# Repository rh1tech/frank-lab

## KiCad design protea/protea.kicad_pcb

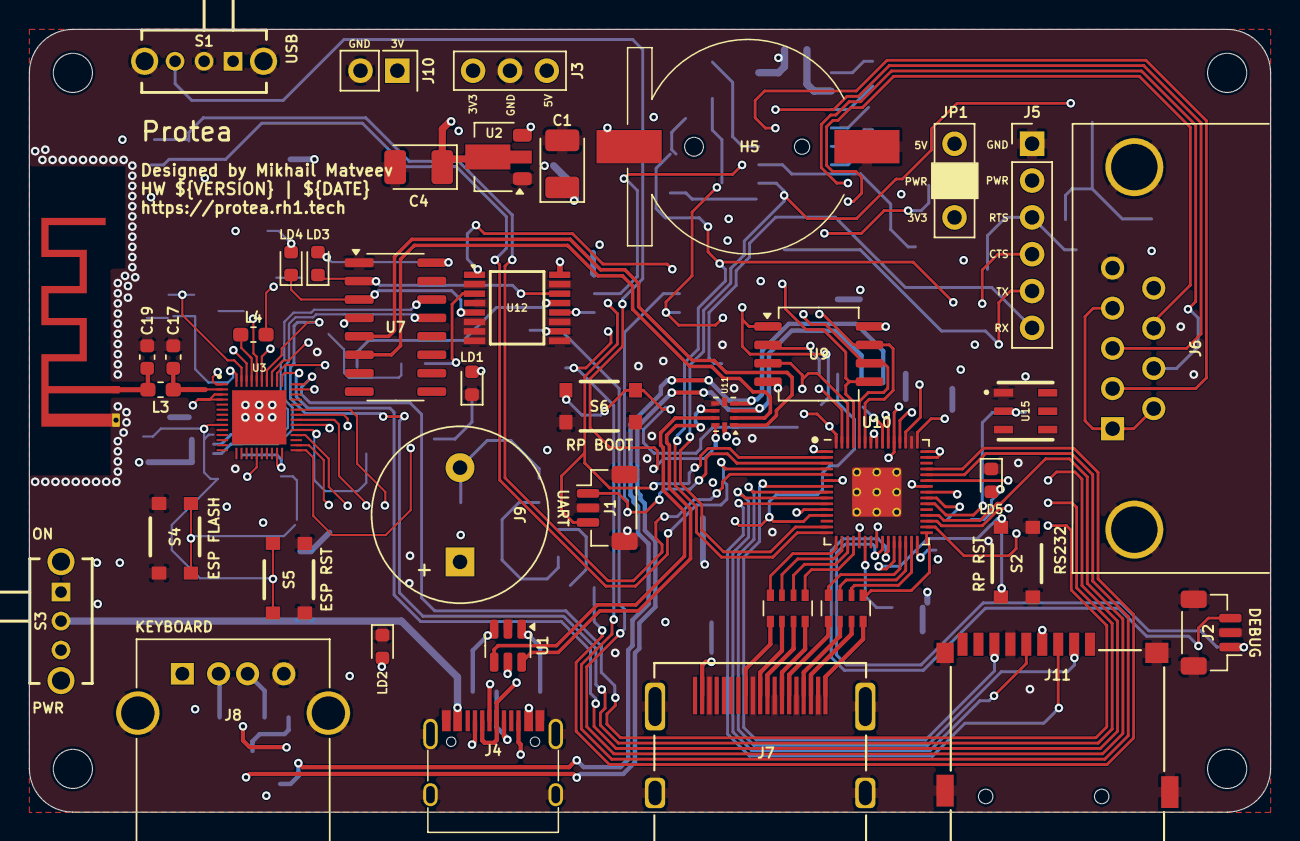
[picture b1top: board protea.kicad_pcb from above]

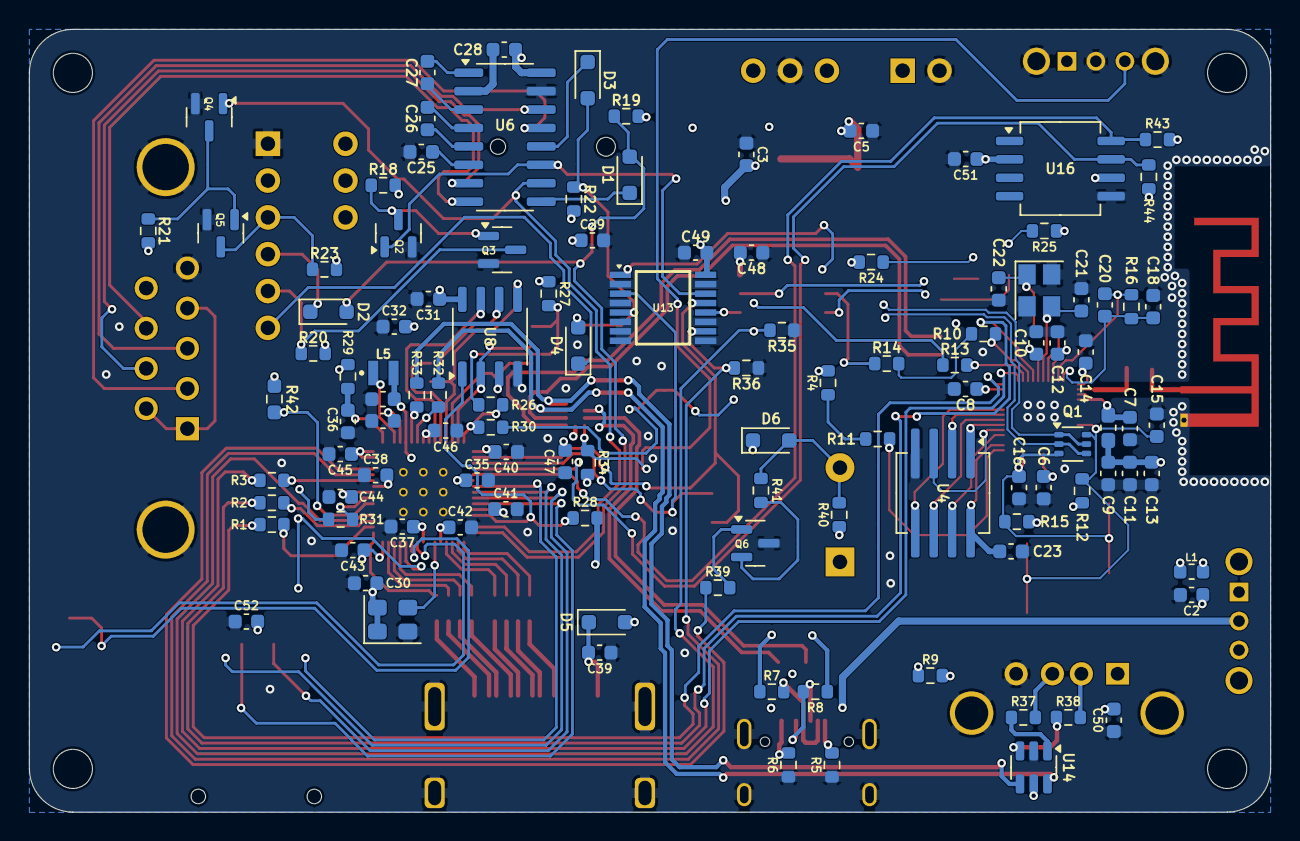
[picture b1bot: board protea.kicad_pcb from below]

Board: 4 copper layers, 85.6 x 54.0 mm, 159 parts (113 on the bottom side), 139 nets.

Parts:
AE1: Antenna_Shield; Antenna_2.4GHz
C1, C4: 22u; CP_Tantalum_3528-12
C2, C3, C5, C29, C30, C31, C32, C35, C38, C39, C40, C41, C42, C43, C44, C45, C46, C47, C51, C52: 100n; C_0603_1608Metric
C6, C13: 1u; C_0603_1608Metric_HandSolder
C7, C9, C10, C12, C14, C23: 100n; C_0603_1608Metric_HandSolder
C8: 100p; C_0603_1608Metric_HandSolder
C11: 10u; C_0603_1608Metric_HandSolder
C15, C16: 1n; C_0603_1608Metric_HandSolder
C17: 1.5pF; C_0603_1608Metric_HandSolder
C18: 10n; C_0603_1608Metric_HandSolder
C19: 2.4pF; C_0603_1608Metric_HandSolder
C20: 3.3n; C_0603_1608Metric_HandSolder
C21, C22: 12p; C_0603_1608Metric_HandSolder
C25, C26, C27, C28: 1u; C_0603_1608Metric_Small
C33, C34, C36, C37: 4.7u; C_0603_1608Metric
C48, C49: 100n; C_0603_1608Metric_Small
C50: 10u; C_0603_1608Metric
D1, D2, D3, D4: 1N4148; D_SOD-323_Alt
D5: 1N5819WS; D_SOD-323
D6: 1N4148; D_SOD-323
H1, H2, H3, H4: Hole 2.7mm; MountingHole_2.7mm
H5: S8411-45R_1; Battery_CR1220
J1: UART; JST_SH_1x03_P1.00mm_Vertical
J2: DEBUG; JST_SH_1x03_P1.00mm_Vertical
J3: PWR; PinHeader_1x03_P2.54mm
J4: USB4215-03-A; USB_C_Receptacle
J5: TTL; PinHeader_1x06_P2.54mm_Vertical
J6: D-SUB 9 Male; DSUB-9_Male_TopMount
J7: DC3RX19JA2; HDMI_Female
J8: 676430910; USB_A_Single
J9: Buzzer; Buzzer_12x8.5RM6.5
J10: BAT 3V; PinHeader_1x02_P2.54mm_Vertical
J11: 104031-0811; MicroSD_SMD_Long
JP1: TTL PWR; PinHeader_1x03_P2.54mm_Vertical
L1: 330R; L_0603_1608Metric
L2: 2nH; Inductor_0603_1608Metric_HandSolder
L3: 2.7nH/0R; Inductor_0603_1608Metric_HandSolder
L4: 24nH/0R; Inductor_0603_1608Metric_HandSolder
L5: 3.3u; L_pol_2016
LD1, LD5: Blue; LED_0603_1608Metric
LD2: Green; LED_0603_1608Metric
LD3, LD4: Orange; LED_0603_1608Metric
Q1: UMH3N; SOT-363
Q2, Q3, Q4, Q5: 2N7000; SOT-23-2N7000
Q6: BC847; SOT-23
R1, R2, R3, R9, R30, R31, R39: 1K; R_0603_1608Metric
R4: 470R; R_0603_1608Metric
R5, R6: 5.1K; R_0603_1608Metric
R7, R8, R37, R38, R41: 22R; R_0603_1608Metric
R10: 499R; R_0603_1608Metric_HandSolder
R11: 0R; R_0603_1608Metric_HandSolder
R12, R15: 10K; R_0603_1608Metric_HandSolder
R13, R14: 330R; R_0603_1608Metric_HandSolder
R16: 20K; R_0603_1608Metric_HandSolder
R18, R19, R21, R22: 1K; R_0603_1608Metric_Small
R20, R23: 470R; R_0603_1608Metric_Small
R24, R25: 1.5K; R_0603_1608Metric
R26: 0R; R_0603_1608Metric
R27, R28, R34: 10K; R_0603_1608Metric
R29: 33R; R_0603_1608Metric
R32, R33: 27R; R_0603_1608Metric
R35, R36: 10K; R_0603_1608Metric_Small
R40: 300R; R_0603_1608Metric
R42: 4.7K; R_0603_1608Metric_Alt
R43, R44: 4.7K; R_0603_1608Metric
RN1, RN2: 270R; R_Array_4x0603
S1: SK12D07VG3NS; SK12D07VG3NS_USB
S2: RP Reset; KMR_2
S3: SK12D07VG3NS; SK12D07VG3NS_PWR
S4: ESP Flash; KMR_2
S5: ESP Boot; KMR_2
S6: RP BOOT; KMR_2
U1, U14: USBLC6-2SC6; SOT-23-6
U2: AMS1117-3.3; SOT-89-3
U3: ESP32-D0WD-V3; QFN35P500X500X90-49N-D
U4: W25Q32JVSIQ; SOIC-8_Longer
U6: MAX232CSE+; SOP-16
U7: CH340C; SOP-16
U8: ESP-PSRAM32; SO-8
U9: W25Q128JVS; SOIC-8
U10: RP2350; QFN-60_RP2350A
U11: TS3USB221RSER; UQFN-10
U12, U13: 74HC4052; SOP65P640X110-16N
U15: DS2401P+; TSOC-6
U16: DS3231MZ; SOIC-8
Y1: 40MHz; Crystal_SMD_3225-4Pin_3.2x2.5mm
Y2: ASE-12MHz; Oscillator_SMD_4Pin_3.2x2.5mm

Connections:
+1V1: C34.1, C35.1, C37.1, C38.1, L5.1, U10.6 (DVDD), U10.23 (DVDD), U10.39 (DVDD), U10.50 (VREG_FB)
+3.3VP: C7.1, L2.2, U3.3 (VDD3P3_1), U3.4 (VDD3P3_2)
+3V3: C4.1, C5.2, C6.1, C8.1, C9.1, C10.1, C11.1, C12.1, C13.1, C14.1, C29.1, C30.1, C31.1, C32.1, C33.1, C40.1, C41.1, C42.1, C43.1, C44.1, C45.1, C46.1, C47.2, C48.2, C49.2, C51.1, C52.2, J3.1, J11.4 (VDD), JP1.3, L2.1, R9.2, R12.2, R15.2, R18.2, R19.2, R21.2, R22.2, R24.2, R25.1, R27.1, R28.2, R29.1, R34.1, R42.1, R43.2, R44.2, U2.2 (VO), U3.1 (VDDA_1), U3.19 (VDD3P3_RTC), U3.37 (VDD3P3_CPU), U3.43 (VDDA_2), U3.46 (VDDA_3), U7.4 (3V), U7.16 (VCC), U8.8 (VCC), U9.8 (VCC), U10.1 (IOVDD), U10.11 (IOVDD), U10.20 (IOVDD), U10.30 (IOVDD), U10.38 (IOVDD), U10.44 (ADC_AVDD), U10.45 (IOVDD), U10.49 (VREG_VIN), U10.53 (USB_OTP_VDD), U10.54 (QSPI_IOVDD), U11.10 (VCC), U12.16 (VCC), U13.16 (VCC), U16.2 (VCC), Y2.1 (EN), Y2.4 (Vdd)
/CH340C/D+: U7.5 (D+), U11.1 (1D+)
/CH340C/D-: U7.6 (D-), U11.2 (1D-)
/CH340C/DTR: Q1.2 (B1), Q1.4 (E2), U7.13 (DTR)
/CH340C/RTS: Q1.1 (E1), Q1.5 (B2), U7.14 (RTS)
/CH340C/RXD: LD4.1 (K), U7.3 (RxD), U12.5 (2Y1)
/CH340C/TXD: LD3.1 (K), U7.2 (TxD), U12.14 (1Y1)
/DS2401P+/DATA: R42.2, U10.36 (GPIO24), U15.2 (DATA)
/ESP32/ANT: AE1.1 (A), C19.1, L3.1
/ESP32/CAP1: C18.1, C20.1, R16.2, U3.48 (CAP1)
/ESP32/CAP2: C20.2, R16.1, U3.47 (CAP2)
/ESP32/GPIO16: R4.1, R11.2
/ESP32/GPIO19: R1.2, U3.38 (GPIO19)
/ESP32/GPIO21: R2.2, U3.42 (GPIO21)
/ESP32/GPIO22: R3.2, U3.39 (GPIO22)
/ESP32/LNA_IN: C17.1, L3.2, U3.2 (LNA_IN)
/ESP32/RXD: R13.1, U12.13 (1Z)
/ESP32/SCK/CLK: U3.31 (SD_CLK), U4.6 (CLK)
/ESP32/SCS/CMD: U3.30 (SD_CMD), U4.1 (~CS)
/ESP32/SDI/SD1: U3.33 (SD_DATA_1), U4.5 (DI(IO0))
/ESP32/SDO/SD0: U3.32 (SD_DATA_0), U4.2 (DO(IO1))
/ESP32/SHD/SD2: U3.28 (SD_DATA_2), U4.7 (IO3)
/ESP32/SWP/SD3: U3.29 (SD_DATA_3), U4.3 (IO2)
/ESP32/TXD: R14.1, U12.3 (2Z)
/ESP32/U0RXD: R13.2, U3.40 (U0RXD)
/ESP32/U0TXD: R10.2, R14.2
/ESP32/VDD_SDIO: C23.1, U3.26 (VDD_SDIO), U4.8 (VCC)
/ESP32/XTAL_N: C21.1, U3.44 (XTAL_N), Y1.3
/ESP32/XTAL_P: L4.1, U3.45 (XTAL_P)
/ESP Buttons/ESP_FLASH: C16.1, Q1.3 (C2), R15.1, S4.2, S4.4, U3.23 (GPIO0)
/ESP Buttons/ESP_RESET: C15.1, Q1.6 (C1), R12.1, S5.2, S5.4, U3.9 (CHIP_PU)
/GPIO0: J1.1, U10.2 (GPIO0), U13.13 (1Z)
/GPIO1: J1.3, U10.3 (GPIO1), U13.3 (2Z)
/GPIO2: R44.1, U10.4 (GPIO2), U16.7 (SDA)
/GPIO3: R43.1, U10.5 (GPIO3), U16.8 (SCL)
/GPIO4: J11.7 (DAT0), U10.7 (GPIO4)
/GPIO5: J11.2 (DAT3/CD), U10.8 (GPIO5)
/GPIO6: J11.5 (CLK), U10.9 (GPIO6)
/GPIO7: J11.3 (CMD), U10.10 (GPIO7)
/GPIO10: Q4.2 (G), U6.10 (T2IN), U10.14 (GPIO10)
/GPIO11: D1.2 (A), D2.2 (A), R19.1, U10.15 (GPIO11)
/GPIO12: RN1.4 (R4.1), U10.16 (GPIO12)
/GPIO13: RN1.3 (R3.1), U10.17 (GPIO13)
/GPIO14: RN1.2 (R2.1), U10.18 (GPIO14)
/GPIO15: RN1.1 (R1.1), U10.19 (GPIO15)
/GPIO16: RN2.4 (R4.1), U10.27 (GPIO16)
/GPIO17: RN2.3 (R3.1), U10.28 (GPIO17)
/GPIO18: RN2.2 (R2.1), U10.29 (GPIO18)
/GPIO19: RN2.1 (R1.1), U10.31 (GPIO19)
/GPIO20: R1.1, U10.32 (GPIO20)
/GPIO21: R2.1, U10.33 (GPIO21)
/GPIO22: R35.2, U10.34 (GPIO22), U12.10 (S0)
/GPIO26: R3.1, U10.40 (GPIO26_ADC0)
/GPIO27: R36.2, U10.41 (GPIO27_ADC1), U13.10 (S0)
/GPIO28: R39.1, U10.42 (GPIO28_ADC2)
/Multiplexers/MP_RX: U12.12 (1Y0), U13.12 (1Y0)
/Multiplexers/MP_TX: U12.1 (2Y0), U13.1 (2Y0)
/Multiplexers/RS232_RX: Q2.2 (G), U6.11 (T1IN), U13.14 (1Y1)
/Multiplexers/RS232_TX: D3.2 (A), D4.2 (A), R22.1, U13.5 (2Y1)
/Power/D+: U1.4 (I/O2), U11.8 (D+)
/Power/D-: U1.6 (I/O1), U11.7 (D-)
/Power/VBUS_IN: J4.2 (VBUS), J4.11 (VBUS), S3.2
/RP2350A/D+: R32.1, U11.3 (2D+), U14.6 (I/O1)
/RP2350A/D-: R33.1, U11.4 (2D-), U14.4 (I/O2)
/RP2350A/FLASH_SS: R26.2, R27.2, U9.1 (~CS)
/RP2350A/GPIO8: R28.1, U8.1 (~CE), U10.12 (GPIO8)
/RP2350A/QSPI_SCLK: U8.6 (SCLK), U9.6 (CLK), U10.56 (QSPI_SCLK)
/RP2350A/QSPI_SD0: U8.5 (SI/SIO), U9.5 (DI(IO0)), U10.57 (QSPI_SD0)
/RP2350A/QSPI_SD1: U8.2 (SO/SIO), U9.2 (DO(IO1)), U10.59 (QSPI_SD1)
/RP2350A/QSPI_SD2: U8.3 (SIO2), U9.3 (IO2), U10.58 (QSPI_SD2)
/RP2350A/QSPI_SD3: U8.7 (SIO3), U9.7 (IO3), U10.55 (QSPI_SD3)
/RP2350A/QSPI_SS: R26.1, R30.1, U10.60 (QSPI_SS)
/RP2350A/SWCLK: J2.3, U10.24 (SWCLK)
/RP2350A/SWD: J2.1, U10.25 (SWD)
/RP2350A/VREG_AVDD: C36.1, R29.2, U10.46 (VREG_AVDD)
/RP2350A/VREG_LX: L5.2, U10.48 (VREG_LX)
/RP2350A/XIN: U10.21 (XIN), Y2.3 (OUT)
/RP2350A/~USB_BOOT: R30.2, S6.2, S6.4
/RS232+TTL/C1+: C27.2, U6.1 (C1+)
/RS232+TTL/C1-: C27.1, U6.3 (C1-)
/RS232+TTL/C2+: C26.2, U6.4 (C2+)
/RS232+TTL/C2-: C26.1, U6.5 (C2-)
/RS232+TTL/CTS_IN: J6.7, U6.7 (T2OUT)
/RS232+TTL/CTS_MAX: D1.1 (K), U6.9 (R2OUT)
/RS232+TTL/CTS_TTL: D2.1 (K), J5.4
/RS232+TTL/RTS_IN: J6.8, U6.8 (R2IN)
/RS232+TTL/RTS_TTL: J5.3, Q5.3 (D), R23.1
/RS232+TTL/RX_IN: J6.3, U6.14 (T1OUT)
/RS232+TTL/RX_MAX: D3.1 (K), U6.12 (R1OUT)
/RS232+TTL/RX_TTL: D4.1 (K), J5.6
/RS232+TTL/TX_IN: J6.2, U6.13 (R1IN)
/RS232+TTL/TX_TTL: J5.5, Q3.3 (D), R20.1
/RS232+TTL/V+: C28.1, U6.2 (V+)
/RS232+TTL/V-: C25.1, U6.6 (V-)
/RS232+TTL/VTTL: J5.2, JP1.2, R20.2, R23.2
/RUN: S2.2, S2.4, U10.26 (RUN)
/USB Multiplx/S: R34.2, S1.3, U11.9 (S)
GND: AE1.2 (Shield), C1.2, C2.2, C3.1, C4.2, C5.1, C6.2, C7.2, C8.2, C9.2, C10.2, C11.2, C12.2, C13.2, C14.2, C15.2, C16.2, C17.2, C18.2, C19.2, C21.2, C22.2, C23.2, C25.2, C29.2, C30.2, C31.2, C32.2, C33.2, C34.2, C35.2, C36.2, C37.2, C38.2, C39.2, C40.2, C41.2, C42.2, C43.2, C44.2, C45.2, C46.2, C47.1, C48.1, C49.1, C50.1, C51.2, C52.1, H5.2 (-), J1.2, J2.2, J3.2, J4.1 (GND), J4.12 (GND), J4.13 (SHIELD), J5.1, J6.5, J7.2 (G_D2), J7.5 (G_D1), J7.8 (G_D0), J7.11 (G_CLK), J7.17 (G_DDC/CEC), J7.20 (SHIELD1), J7.21 (SHIELD2), J7.22 (SHIELD3), J7.23 (SHIELD4), J8.4 (GND), J8.5 (Shield), J10.2, J11.6 (VSS), J11.SH (SHIELD), LD1.1 (K), LD2.1 (K), LD5.1 (K), Q2.1 (S), Q3.1 (S), Q4.1 (S), Q5.1 (S), Q6.3 (E), R5.1, R6.1, R35.1, R36.1, S1.2, S2.1, S2.3, S4.1, S4.3, S5.1, S5.3, S6.1, S6.3, U1.2 (GND), U2.1 (GND), U3.49 (GND), U4.4 (GND), U6.15 (GND), U7.1 (GND), U8.4 (VSS), U9.4 (GND), U10.47 (VREG_PGND), U10.61 (GND), U11.5 (GND), U11.6 (~OE), U12.2 (2Y2), U12.4 (2Y3), U12.6 (~E), U12.7 (VEE), U12.8 (GND), U12.9 (S1), U12.11 (1Y3), U12.15 (1Y2), U13.2 (2Y2), U13.4 (2Y3), U13.6 (~E), U13.7 (VEE), U13.8 (GND), U13.9 (S1), U13.11 (1Y3), U13.15 (1Y2), U14.2 (GND), U15.1 (GND), U16.5 (GND), Y1.2, Y1.4, Y2.2 (GND)
GPIO25: R31.2, U10.37 (GPIO25)
unnamed: C2.1, L1.2, S3.1
unnamed: C22.1, L4.2, Y1.1
unnamed: C39.1, D5.1 (K), J7.18 (+5V)
unnamed: D6.2 (A), J9.2 (-), R40.2, R41.1
unnamed: H5.1 (+), J10.1, U16.6 (VBAT)
unnamed: J4.4 (CC1), R5.2
unnamed: J4.10 (CC2), R6.2
unnamed: J4.5 (DN2), J4.7 (DN1), R7.2
unnamed: J4.6 (DP1), J4.8 (DP2), R8.2
unnamed: J6.1, J6.4, J6.6
unnamed: J7.12 (CLKN), RN1.5 (R4.2)
unnamed: J7.10 (CLKP), RN1.6 (R3.2)
unnamed: J7.9 (D0N), RN1.7 (R2.2)
unnamed: J7.7 (D0P), RN1.8 (R1.2)
unnamed: J7.6 (D1N), RN2.5 (R4.2)
unnamed: J7.4 (D1P), RN2.6 (R3.2)
unnamed: J7.3 (D2N), RN2.7 (R2.2)
unnamed: J7.1 (D2P), RN2.8 (R1.2)
unnamed: J8.3 (D+), R37.2
unnamed: J8.2 (D-), R38.2
unnamed: LD1.2 (A), R4.2
unnamed: LD2.2 (A), R9.1
unnamed: LD3.2 (A), R24.1
unnamed: LD4.2 (A), R25.2
unnamed: LD5.2 (A), R31.1
unnamed: Q2.3 (D), Q3.2 (G), R18.1
unnamed: Q4.3 (D), Q5.2 (G), R21.1
unnamed: Q6.2 (B), R39.2
unnamed: Q6.1 (C), R41.2
unnamed: R7.1, U1.1 (I/O1)
unnamed: R8.1, U1.3 (I/O2)
unnamed: R37.1, U14.1 (I/O1)
unnamed: R38.1, U14.3 (I/O2)
unnamed: R11.1, U3.25 (GPIO16)
unnamed: R10.1, U3.41 (U0TXD)
unnamed: R33.2, U10.51 (USB_DM)
unnamed: R32.2, U10.52 (USB_DP)
VBUS: C1.1, C3.2, C28.2, C50.2, D5.2 (A), D6.1 (K), J3.3, J8.1 (VBUS), J9.1 (+), JP1.1, L1.1, R40.1, U1.5 (VBUS), U2.3 (VI), U6.16 (VCC), U14.5 (VBUS)

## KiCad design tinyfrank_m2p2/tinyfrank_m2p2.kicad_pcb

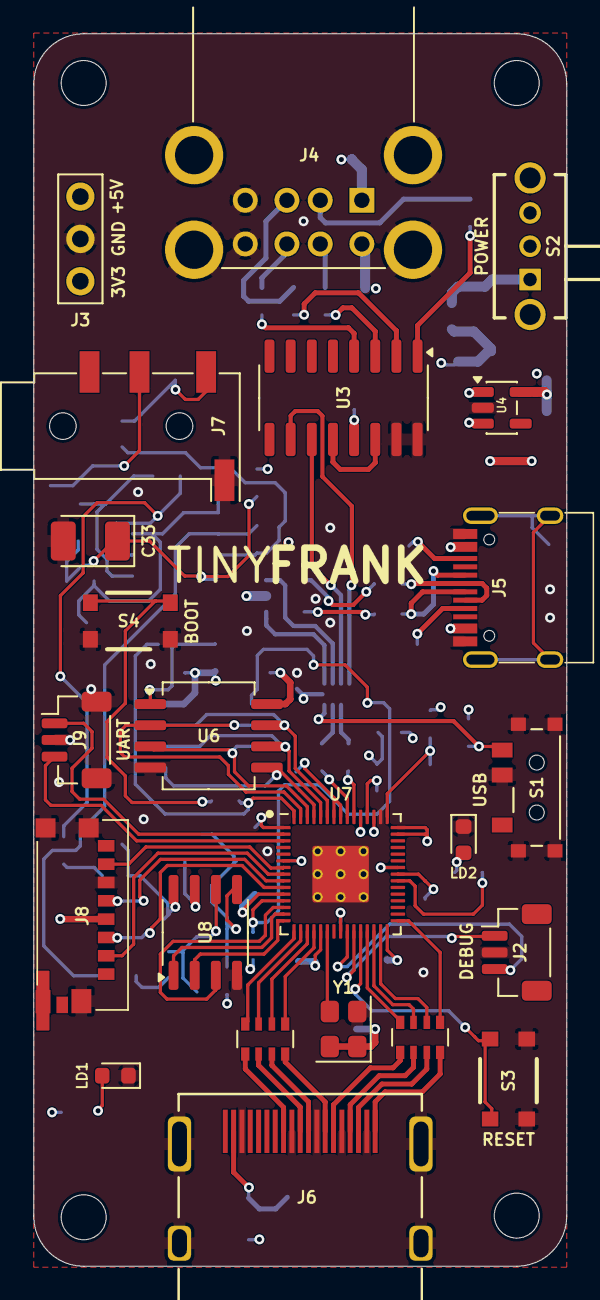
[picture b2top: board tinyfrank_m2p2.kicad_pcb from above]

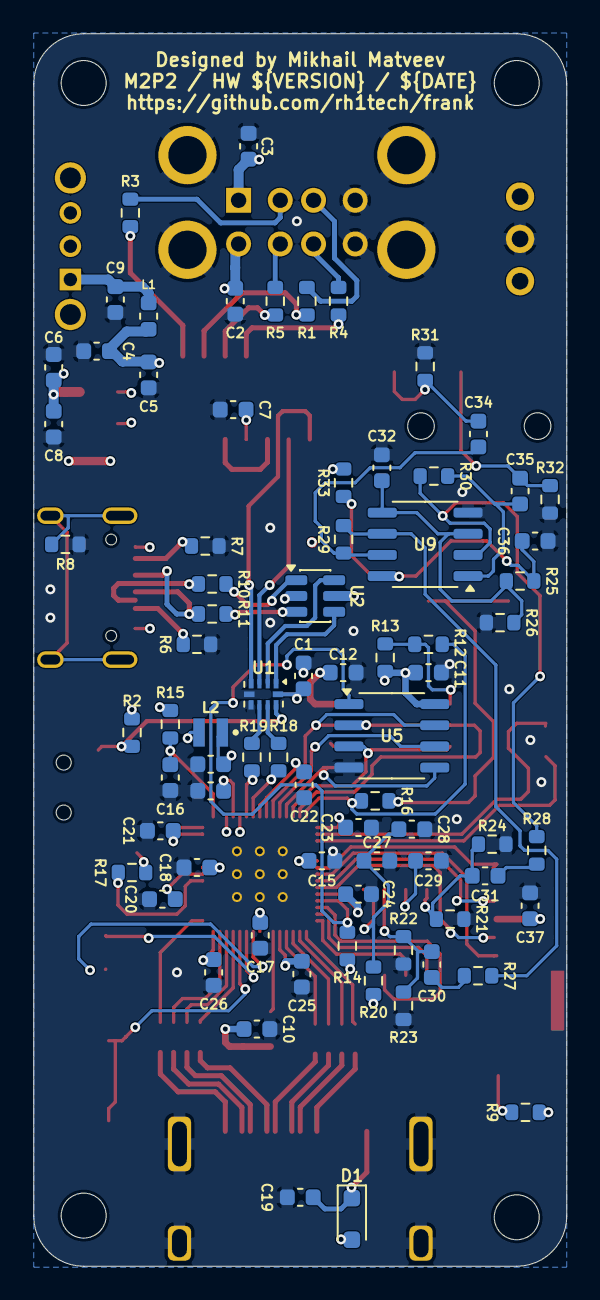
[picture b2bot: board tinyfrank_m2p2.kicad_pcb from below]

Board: 4 copper layers, 32.0 x 74.0 mm, 103 parts (76 on the bottom side), 89 nets.

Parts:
C1, C5, C6, C9, C10, C11, C12, C15, C18, C19, C20, C21, C22, C23, C24, C25, C26, C28, C36, C37: 100n; C_0603_1608Metric
C2, C3, C4, C8, C27, C29, C30, C31, C32, C34, C35: 10u; C_0603_1608Metric
C7, C13, C14, C16, C17: 4.7u; C_0603_1608Metric
C33: 10u; C_3528_Tantalum
D1: 1N5819WS; D_SOD-323
H1, H2, H3, H4: Hole 2.7mm; MountingHole_2.7mm
J2, J9: DEBUG; JST_SH_1x03_P1.00mm_Vertical
J3: PWR; PinHeader_1x03_P2.54mm
J4: SS-52100-004; USB_A_Stacked
J5: USB4215-03-A; USB_C_Receptacle
J6: DC3RX19JA2; HDMI_Female
J7: PJ-320D; AudioJack_3.5mm_PJ320D
J8: 0475710001; MicroSD_SMD_Short
L1: 330R; L_0603_1608Metric
L2: 3.3u; L_2016_Polarized
LD1: Green; LED_0603_1608Metric
LD2: Blue; LED_0603_1608Metric
R1, R3, R4, R5, R10, R11: 22R; R_0603_1608Metric
R2, R13, R14, R23, R24, R25, R26, R27, R28: 10K; R_0603_1608Metric
R6, R7: 5.1K; R_0603_1608Metric
R8: 1M; R_0603_1608Metric
R9, R16, R17: 1K; R_0603_1608Metric
R12: 0R; R_0603_1608Metric
R15: 33R; R_0603_1608Metric
R18, R19: 27R; R_0603_1608Metric
R20, R33: 100R; R_0603_1608Metric
R21, R22: 470R; R_0603_1608Metric
R29, R30: 47K; R_0603_1608Metric
R31, R32: 20K; R_0603_1608Metric
RN1, RN2: 270R; R_Array_4x0603
S1: MSK12C02; Switch_Slide_MSK12C02
S2: SK12D07VG3NS; Switch_Slide_SK12D07VG3NS
S3, S4: Button; Button_SMD_3x4x2mm
U1: TS3USB221RSER; UQFN-10
U2: USBLC6-2SC6; SOT-23-6
U3: MW7211A; SOP-16_P1.27mm
U4: ME6211C33M5; SOT-23-5
U5: ESP-PSRAM32; SO-8
U6: W25Q128JVS; SOIC-8
U7: RP2350; QFN-60_RP2350A
U8: TDA1387T; SO-8
U9: LM358; SO-8
Y1: ASE-12MHz; Oscillator_SMD_Abracon_ASE-4Pin_3.2x2.5mm

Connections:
+1V1: C14.1, C15.1, C17.1, C18.1, L2.1, U7.6 (DVDD), U7.23 (DVDD), U7.39 (DVDD), U7.50 (VREG_FB)
+3V3: C1.2, C6.1, C8.1, C10.1, C11.1, C12.1, C13.1, C20.1, C21.1, C22.1, C23.1, C24.1, C25.1, C26.1, C37.2, J3.1, J8.P4 (VDD), R2.1, R9.2, R13.1, R14.2, R15.1, U1.10 (VCC), U4.5 (V_{OUT}), U5.8 (VCC), U6.8 (VCC), U7.1 (IOVDD), U7.11 (IOVDD), U7.20 (IOVDD), U7.30 (IOVDD), U7.38 (IOVDD), U7.44 (ADC_AVDD), U7.45 (IOVDD), U7.49 (VREG_VIN), U7.53 (USB_OTP_VDD), U7.54 (QSPI_IOVDD), Y1.1 (EN), Y1.4 (Vdd)
/Audio/AMP_OUTL: C34.2, J7.T, R31.2
/Audio/AMP_OUTR: C35.2, J7.R, R32.2
/Audio/TDA_DATA: U7.13 (GPIO9), U8.3 (DATA)
/Audio/TDA_L: C30.1, R22.2, R23.1, U8.6 (A_LEFT)
/Audio/TDA_LRCK: U7.15 (GPIO11), U8.2 (LRCK)
/Audio/TDA_R: C31.1, R21.1, R24.1, U8.8 (A_RIGHT)
/Audio/TDA_SCLK: U7.14 (GPIO10), U8.1 (SCLK)
/HDMI/CLKN: RN1.4 (R4.1), U7.16 (GPIO12)
/HDMI/CLKP: RN1.3 (R3.1), U7.17 (GPIO13)
/HDMI/D0N: RN1.2 (R2.1), U7.18 (GPIO14)
/HDMI/D0P: RN1.1 (R1.1), U7.19 (GPIO15)
/HDMI/D1N: RN2.4 (R4.1), U7.27 (GPIO16)
/HDMI/D1P: RN2.3 (R3.1), U7.28 (GPIO17)
/HDMI/D2N: RN2.2 (R2.1), U7.29 (GPIO18)
/HDMI/D2P: RN2.1 (R1.1), U7.31 (GPIO19)
/Micro SD/CDDAT3: J8.P2 (CD/DAT3), U7.8 (GPIO5)
/Micro SD/CLK: J8.P5 (CLK), U7.9 (GPIO6)
/Micro SD/CMD: J8.P3 (CMD), U7.10 (GPIO7)
/Micro SD/DAT0: J8.P7 (DAT0), U7.7 (GPIO4)
/Power/D1+: U1.1 (1D+), U2.4 (I/O2)
/Power/D1-: U1.2 (1D-), U2.6 (I/O1)
/Power/D2+: U1.3 (2D+), U3.11 (DPU)
/Power/D2-: U1.4 (2D-), U3.10 (DMU)
/Power/D+: R18.1, U1.8 (D+)
/Power/D-: R19.1, U1.7 (D-)
/Power/DS1+: R1.1, U3.2 (DP0)
/Power/DS1-: R3.1, U3.1 (DM0)
/Power/DS2+: R4.1, U3.4 (DP1)
/Power/DS2-: R5.1, U3.3 (DM1)
/Power/S: R2.2, S1.3, U1.9 (S)
/Power/VBUS_IN: J5.2 (VBUS), J5.11 (VBUS), S2.2
/RP2350A/FLASH_SS: R12.2, R13.2, U6.1 (~CS)
/RP2350A/GPIO0: J9.1, U7.2 (GPIO0)
/RP2350A/GPIO1: J9.3, U7.3 (GPIO1)
/RP2350A/GPIO8: R14.1, U5.1 (~CE), U7.12 (GPIO8)
/RP2350A/QSPI_SCLK: U5.6 (SCLK), U6.6 (CLK), U7.56 (QSPI_SCLK)
/RP2350A/QSPI_SD0: U5.5 (SI/SIO), U6.5 (DI(IO0)), U7.57 (QSPI_SD0)
/RP2350A/QSPI_SD1: U5.2 (SO/SIO), U6.2 (DO(IO1)), U7.59 (QSPI_SD1)
/RP2350A/QSPI_SD2: U5.3 (SIO2), U6.3 (IO2), U7.58 (QSPI_SD2)
/RP2350A/QSPI_SD3: U5.7 (SIO3), U6.7 (IO3), U7.55 (QSPI_SD3)
/RP2350A/QSPI_SS: R12.1, R16.1, U7.60 (QSPI_SS)
/RP2350A/SWCLK: J2.3, U7.24 (SWCLK)
/RP2350A/SWD: J2.1, U7.25 (SWD)
/RP2350A/VREG_AVDD: C16.1, R15.2, U7.46 (VREG_AVDD)
/RP2350A/VREG_LX: L2.2, U7.48 (VREG_LX)
/RP2350A/XIN: U7.21 (XIN), Y1.3 (OUT)
/RP2350A/~USB_BOOT: R16.2, S4.2, S4.4
/RP Reset/C1: S3.2, S3.4, U7.26 (RUN)
GND: C1.1, C2.2, C3.2, C4.1, C5.1, C6.2, C7.2, C8.2, C9.2, C10.2, C11.2, C12.2, C13.2, C14.2, C15.2, C16.2, C17.2, C18.2, C19.2, C20.2, C21.2, C22.2, C23.2, C24.2, C25.2, C26.2, C27.2, C28.2, C29.2, C32.1, C33.2, C36.1, C37.1, J2.2, J3.2, J4.4 (GND1), J4.8 (GND2), J4.SH (Shield), J5.1 (GND), J5.12 (GND), J6.2 (G_D2), J6.5 (G_D1), J6.8 (G_D0), J6.11 (G_CLK), J6.17 (G_DDC/CEC), J6.20 (SHIELD1), J6.21 (SHIELD2), J6.22 (SHIELD3), J6.23 (SHIELD4), J7.S, J8.P6 (VSS), J8.SH (GND_3), J9.2, LD1.1 (K), LD2.1 (K), R6.1, R7.1, R8.2, R21.2, R22.1, R23.2, R24.2, R26.1, R31.1, R32.1, S1.2, S1.4 (GND_4), S3.1, S3.3, S4.1, S4.3, U1.5 (GND), U1.6 (~OE), U2.2 (GND), U3.15 (GND), U3.16 (GND), U4.2 (V_{SS}), U5.4 (VSS), U6.4 (GND), U7.47 (VREG_PGND), U7.61 (GND), U8.4 (AGND), U9.4 (V-), Y1.2 (GND)
GPIO25: R17.2, U7.37 (GPIO25)
unnamed: C9.1, L1.2, S2.1
unnamed: C30.2, R27.2
unnamed: C31.2, R28.2
unnamed: C34.1, R29.1, U9.7
unnamed: C35.1, R30.1, U9.1
unnamed: C19.1, D1.1 (K), J6.18 (+5V)
unnamed: J4.3 (D1+), R1.2
unnamed: J4.2 (D1-), R3.2
unnamed: J4.7 (D2+), R4.2
unnamed: J4.6 (D2-), R5.2
unnamed: J5.4 (CC1), R6.2
unnamed: J5.10 (CC2), R7.2
unnamed: J5.5 (DN2), J5.7 (DN1), R10.2
unnamed: J5.6 (DP1), J5.8 (DP2), R11.2
unnamed: J5.13 (SHIELD), R8.1
unnamed: J6.12 (CLKN), RN1.5 (R4.2)
unnamed: J6.10 (CLKP), RN1.6 (R3.2)
unnamed: J6.9 (D0N), RN1.7 (R2.2)
unnamed: J6.7 (D0P), RN1.8 (R1.2)
unnamed: J6.6 (D1N), RN2.5 (R4.2)
unnamed: J6.4 (D1P), RN2.6 (R3.2)
unnamed: J6.3 (D2N), RN2.7 (R2.2)
unnamed: J6.1 (D2P), RN2.8 (R1.2)
unnamed: LD1.2 (A), R9.1
unnamed: LD2.2 (A), R17.1
unnamed: R10.1, U2.1 (I/O1)
unnamed: R11.1, U2.3 (I/O2)
unnamed: U3.12 (VD33), U3.14 (VD3)
unnamed: R19.2, U7.51 (USB_DM)
unnamed: R18.2, U7.52 (USB_DP)
unnamed: C29.1, U8.7 (FLT)
unnamed: C27.1, C28.1, R20.1, U8.5 (VA)
unnamed: C32.2, R25.1, R26.2, U9.3 (+), U9.5 (+)
unnamed: R28.1, R30.2, U9.2 (-)
unnamed: R27.1, R29.2, U9.6 (-)
unnamed: C33.1, C36.2, R25.2, R33.2, U9.8 (V+)
VBUS: C2.1, C3.1, C4.2, C5.2, C7.1, D1.2 (A), J3.3, J4.1 (VBUS1), J4.5 (VBUS2), L1.1, R20.2, R33.1, U2.5 (VBUS), U3.13 (VDD5), U4.1 (V_{IN}), U4.3 (CE)

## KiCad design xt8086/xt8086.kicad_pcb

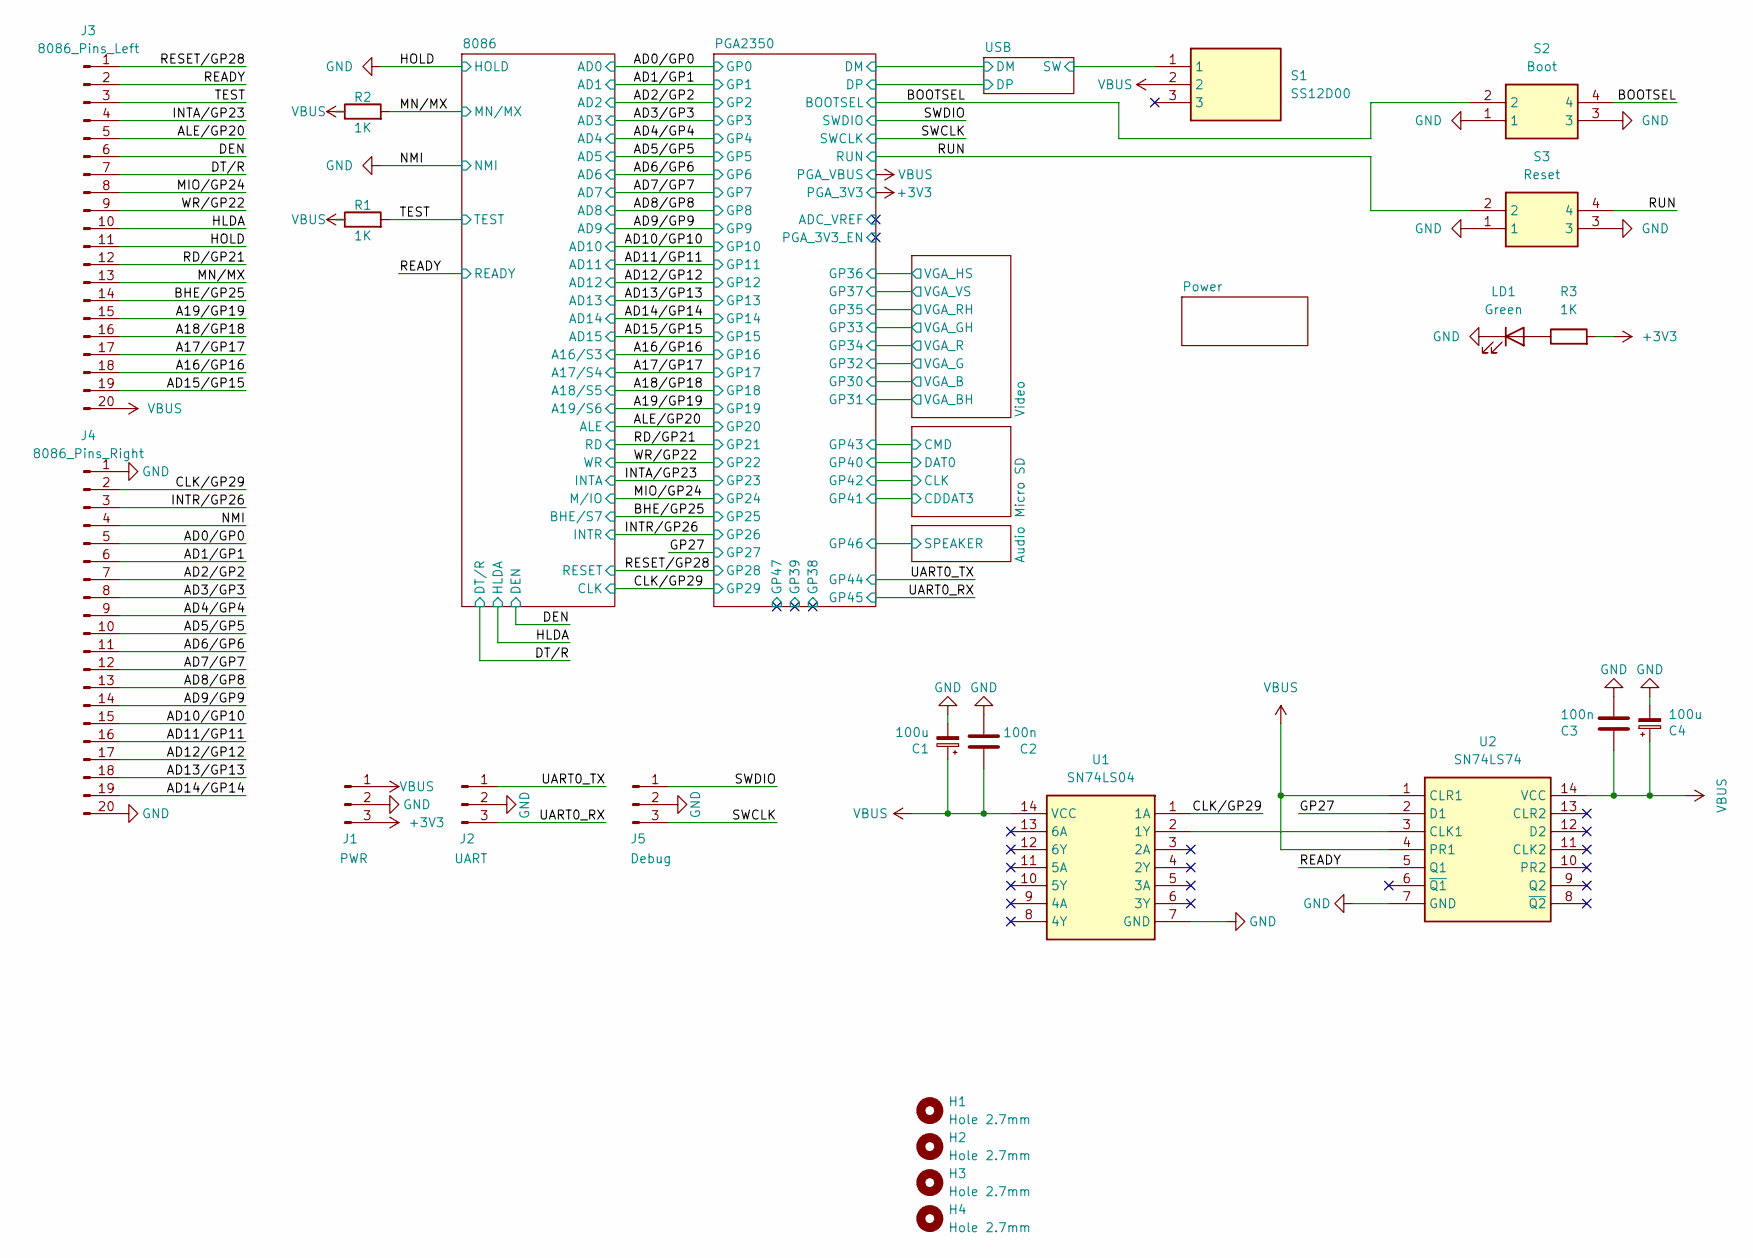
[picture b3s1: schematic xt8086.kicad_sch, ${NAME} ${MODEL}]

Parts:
C1, C4: 100u; CP_Radial_D6.3mm_P2.50mm
C2, C3: 100n; C_0805_2012Metric
H1, H2, H3, H4: Hole 2.7mm; MountingHole_2.7mm
J1: PWR; PinHeader_1x03_P2.54mm_Vertical
J2: UART; JST_SH_1x03_P1.00mm_Vertical
J3: 8086_Pins_Left; PinSocket_1x20_P2.54mm_Vertical
J4: 8086_Pins_Right; PinSocket_1x20_P2.54mm_Vertical
J5: Debug; JST_SH_1x03_P1.00mm_Vertical
LD1: Green; LED_0805_2012Metric_Pad1.15x1.40mm_HandSolder
R1, R2, R3: 1K; R_0805_2012Metric
S1: SS12D00; Switch_Slide_SS12D00; Mouser Part Number 611-SK12D07VG3NS
S2: Boot; Button_SMD_3x4x2mm; Mouser Part Number 611-KMR221G-LFS
S3: Reset; Button_SMD_3x4x2mm; Mouser Part Number 611-KMR221G-LFS
U1: SN74LS04; DIP-14_W7.62mm; Mouser Part Number 595-SN74LS04N
U2: SN74LS74; DIP-14_W7.62mm; Mouser Part Number 595-SN74LS74ANE4

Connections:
+3V3: J1.3, R3.2; also elsewhere on the board
/A16/GP16: J3.18; also elsewhere on the board
/A17/GP17: J3.17; also elsewhere on the board
/A18/GP18: J3.16; also elsewhere on the board
/A19/GP19: J3.15; also elsewhere on the board
/AD0/GP0: J4.5; also elsewhere on the board
/AD1/GP1: J4.6; also elsewhere on the board
/AD2/GP2: J4.7; also elsewhere on the board
/AD3/GP3: J4.8; also elsewhere on the board
/AD4/GP4: J4.9; also elsewhere on the board
/AD5/GP5: J4.10; also elsewhere on the board
/AD6/GP6: J4.11; also elsewhere on the board
/AD7/GP7: J4.12; also elsewhere on the board
/AD8/GP8: J4.13; also elsewhere on the board
/AD9/GP9: J4.14; also elsewhere on the board
/AD10/GP10: J4.15; also elsewhere on the board
/AD11/GP11: J4.16; also elsewhere on the board
/AD12/GP12: J4.17; also elsewhere on the board
/AD13/GP13: J4.18; also elsewhere on the board
/AD14/GP14: J4.19; also elsewhere on the board
/AD15/GP15: J3.19; also elsewhere on the board
/ALE/GP20: J3.5; also elsewhere on the board
/BOOTSEL: S2.2, S2.4; also elsewhere on the board
/CLK/GP29: J4.2, U1.1 (1A); also elsewhere on the board
/DEN: J3.6; also elsewhere on the board
/DT/R: J3.7; also elsewhere on the board
/GP27: U2.2 (D1); also elsewhere on the board
/HLDA: J3.10; also elsewhere on the board
/INTA/GP23: J3.4; also elsewhere on the board
/INTR/GP26: J4.3; also elsewhere on the board
/MIO/GP24: J3.8; also elsewhere on the board
/MN/MX: J3.13, R2.2; also elsewhere on the board
/RD/GP21: J3.12; also elsewhere on the board
/READY: J3.2, U2.5 (Q1); also elsewhere on the board
/RESET/GP28: J3.1; also elsewhere on the board
/RUN: S3.2, S3.4; also elsewhere on the board
/SWCLK: J5.3; also elsewhere on the board
/SWDIO: J5.1; also elsewhere on the board
/TEST: J3.3, R1.2; also elsewhere on the board
/UART0_RX: J2.3; also elsewhere on the board
/UART0_TX: J2.1; also elsewhere on the board
/USB/SW: S1.1; also elsewhere on the board
/WR/GP22: J3.9; also elsewhere on the board
GND: C1.2, C2.2, C3.2, C4.2, J1.2, J2.2, J3.11, J4.1, J4.4, J4.20, J5.2, LD1.1 (K), S2.1, S2.3, S3.1, S3.3, U1.7 (GND), U2.7 (GND); also elsewhere on the board
GP25: J3.14; also elsewhere on the board
unnamed: LD1.2 (A), R3.1
unnamed: U1.2 (1Y), U2.3 (CLK1)
VBUS: C1.1, C2.1, C3.1, C4.1, J1.1, J3.20, R1.1, R2.1, S1.2, U1.14 (VCC), U2.1 (CLR1), U2.4 (PR1), U2.14 (VCC); also elsewhere on the board

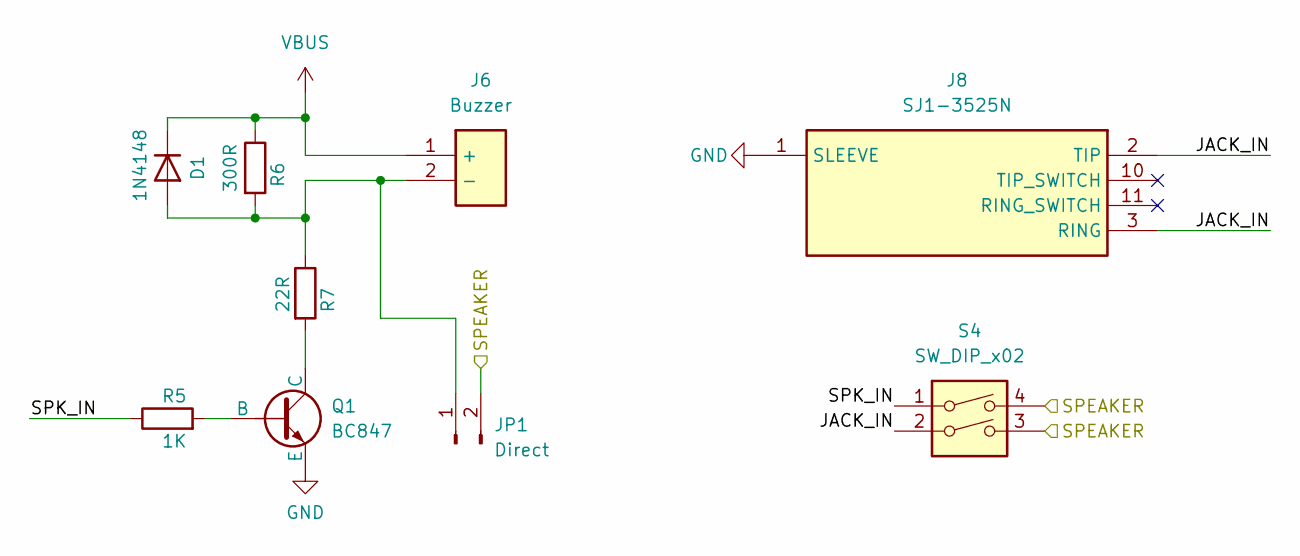
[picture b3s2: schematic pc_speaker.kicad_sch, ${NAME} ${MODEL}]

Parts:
D1: 1N4148; D_SOD-323
J6: Buzzer; Buzzer_12x8.5RM6.5; Mouser Part Number 490-CMT-7525-80SMTTR
J8: SJ1-3525N; AudioJack_3.5mm_SJ1-3525N; Mouser Part Number 490-SJ1-3525N
JP1: Direct; SolderJumper-2_P1.3mm_Open_Pad1.0x1.5mm
Q1: BC847; SOT-23
R5: 1K; R_0805_2012Metric
R6: 300R; R_0805_2012Metric
R7: 22R; R_0805_2012Metric
S4: SW_DIP_x02; SW_DIP_SPSTx02_Slide_9.78x7.26mm_W7.62mm_P2.54mm

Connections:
/Audio/JACK_IN: J8.2 (TIP), J8.3 (RING), S4.2
/Audio/SPEAKER: JP1.2, S4.3, S4.4; also elsewhere on the board
/Audio/SPK_IN: R5.1, S4.1
GND: J8.1 (SLEEVE), Q1.3 (E); also elsewhere on the board
unnamed: D1.2 (A), J6.2 (-), JP1.1, R6.2, R7.1
unnamed: Q1.2 (B), R5.2
unnamed: Q1.1 (C), R7.2
VBUS: D1.1 (K), J6.1 (+), R6.1; also elsewhere on the board

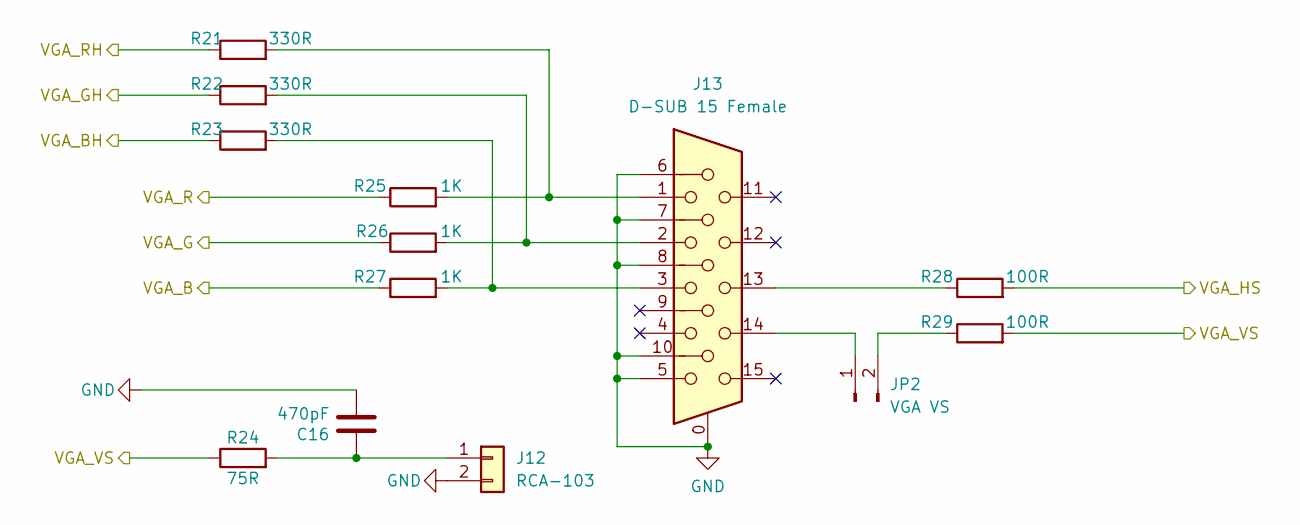
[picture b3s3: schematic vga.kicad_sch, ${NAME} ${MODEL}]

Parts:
C16: 470pF; C_0805_2012Metric
J12: RCA-103; BarrelJack_RCJ-012
J13: D-SUB 15 Female; DSUB-15_Female
JP2: VGA VS; PinHeader_1x02_P2.54mm
R21, R22, R23: 330R; R_0805_2012Metric
R24: 75R; R_0805_2012Metric
R25, R26, R27: 1K; R_0805_2012Metric
R28, R29: 100R; R_0805_2012Metric

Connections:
/PGA2350/GP30: R27.1; also elsewhere on the board
/PGA2350/GP31: R23.1; also elsewhere on the board
/PGA2350/GP32: R26.1; also elsewhere on the board
/PGA2350/GP33: R22.1; also elsewhere on the board
/PGA2350/GP34: R25.1; also elsewhere on the board
/PGA2350/GP35: R21.1; also elsewhere on the board
/PGA2350/GP36: R28.2; also elsewhere on the board
/PGA2350/GP37: R24.1, R29.2; also elsewhere on the board
GND: C16.2, J12.2, J13.0, J13.5, J13.6, J13.7, J13.8, J13.10; also elsewhere on the board
unnamed: C16.1, J12.1, R24.2
unnamed: J13.1, R21.2, R25.2
unnamed: J13.2, R22.2, R26.2
unnamed: J13.3, R23.2, R27.2
unnamed: J13.13, R28.1
unnamed: J13.14, JP2.1
unnamed: JP2.2, R29.1

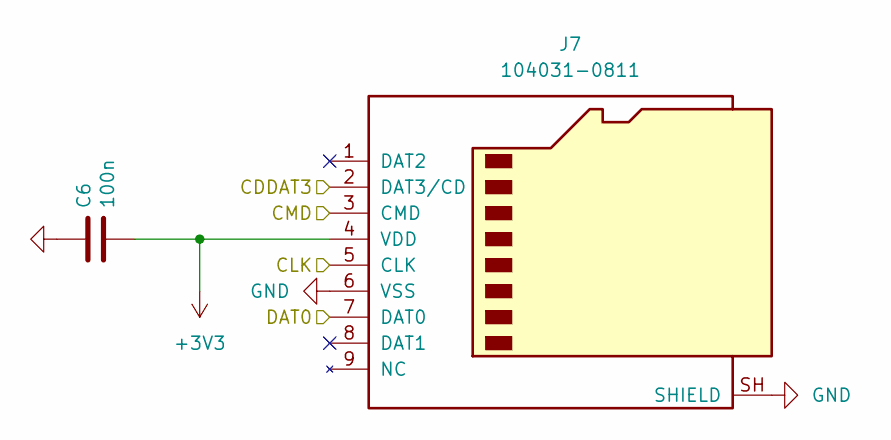
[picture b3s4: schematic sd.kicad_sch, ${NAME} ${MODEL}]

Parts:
C6: 100n; C_0805_2012Metric
J7: 104031-0811; MicroSD_SMD_Long

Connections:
+3V3: C6.2, J7.4 (VDD); also elsewhere on the board
/Micro SD/CDDAT3: J7.2 (DAT3/CD); also elsewhere on the board
/Micro SD/CLK: J7.5 (CLK); also elsewhere on the board
/Micro SD/CMD: J7.3 (CMD); also elsewhere on the board
/Micro SD/DAT0: J7.7 (DAT0); also elsewhere on the board
GND: C6.1, J7.6 (VSS), J7.SH (SHIELD); also elsewhere on the board
